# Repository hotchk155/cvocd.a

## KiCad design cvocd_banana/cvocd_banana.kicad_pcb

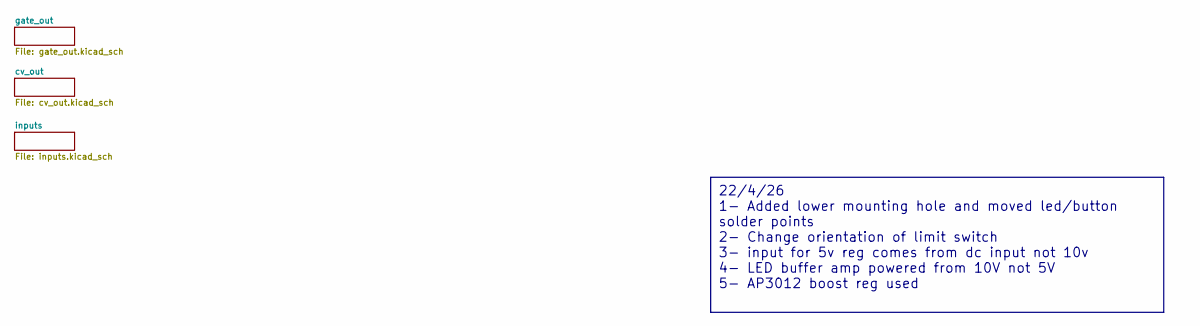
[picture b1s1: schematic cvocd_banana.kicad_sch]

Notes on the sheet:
22/4/26 1- Added lower mounting hole and moved led/button solder points 2- Change orientation of limit switch 3- input for 5v reg comes from dc input not 10v 4- LED buffer amp powered from 10V not 5V 5- AP3012 boost reg used

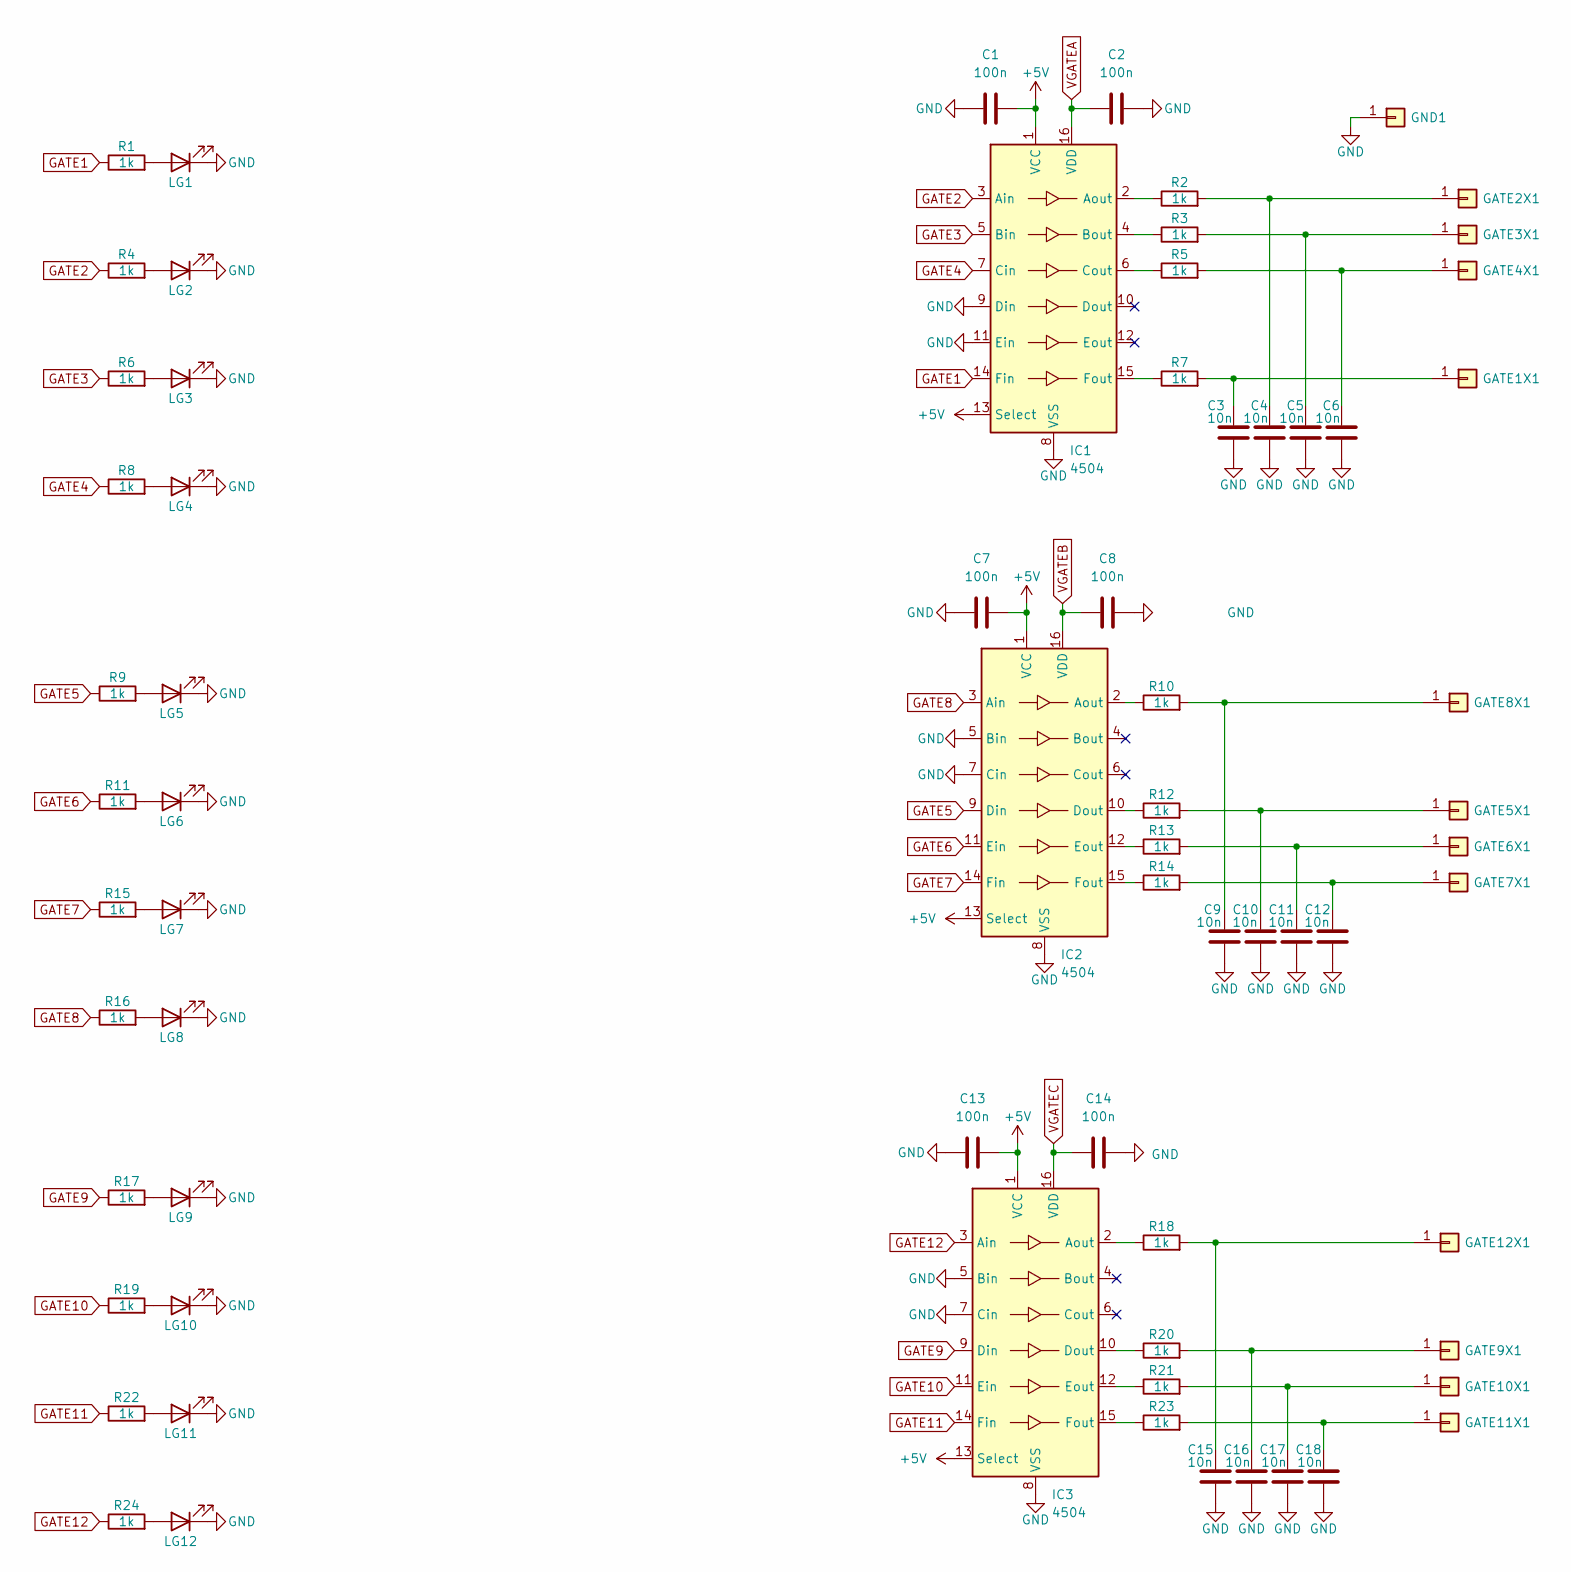
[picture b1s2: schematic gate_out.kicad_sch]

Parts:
C1, C2, C7, C8, C13, C14: 100n; C_0805_2012Metric
C3, C4, C5, C6, C9, C10, C11, C12, C15, C16, C17, C18: 10n; C_0805_2012Metric
GATE1X1, GATE2X1, GATE3X1, GATE4X1, GATE5X1, GATE6X1, GATE7X1, GATE8X1, GATE9X1, GATE10X1, GATE11X1, GATE12X1: Conn_01x01; CINCH-BANANA
GND1: Conn_01x01; CINCH-BANANA
IC1, IC2, IC3: 4504; SOIC-16_3.9x9.9mm_P1.27mm
LG1, LG2, LG3, LG4, LG5, LG6, LG7, LG8, LG9, LG10, LG11, LG12: LED; 3528_ReverseMount_LED
R1, R2, R3, R4, R5, R6, R7, R8, R9, R10, R11, R12, R13, R14, R15, R16, R17, R18, R19, R20, R21, R22, R23, R24: 1k; R_0805_2012Metric

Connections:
+5V: C1.2, C7.2, C13.2, IC1.1 (VCC), IC1.13 (Select), IC2.1 (VCC), IC2.13 (Select), IC3.1 (VCC), IC3.13 (Select); also elsewhere on the board
GATE1: IC1.14 (Fin), R1.1; also elsewhere on the board
GATE2: IC1.3 (Ain), R4.1; also elsewhere on the board
GATE3: IC1.5 (Bin), R6.1; also elsewhere on the board
GATE4: IC1.7 (Cin), R8.1; also elsewhere on the board
GATE5: IC2.9 (Din), R9.1; also elsewhere on the board
GATE6: IC2.11 (Ein), R11.1; also elsewhere on the board
GATE7: IC2.14 (Fin), R15.1; also elsewhere on the board
GATE8: IC2.3 (Ain), R16.1; also elsewhere on the board
GATE9: IC3.9 (Din), R17.1; also elsewhere on the board
GATE10: IC3.11 (Ein), R19.1; also elsewhere on the board
GATE11: IC3.14 (Fin), R22.1; also elsewhere on the board
GATE12: IC3.3 (Ain), R24.1; also elsewhere on the board
GND: C1.1, C2.2, C3.1, C4.1, C5.1, C6.1, C7.1, C8.2, C9.1, C10.1, C11.1, C12.1, C13.1, C14.2, C15.1, C16.1, C17.1, C18.1, GND1.1, IC1.8 (VSS), IC1.9 (Din), IC1.11 (Ein), IC2.5 (Bin), IC2.7 (Cin), IC2.8 (VSS), IC3.5 (Bin), IC3.7 (Cin), IC3.8 (VSS), LG1.1 (K), LG2.1 (K), LG3.1 (K), LG4.1 (K), LG5.1 (K), LG6.1 (K), LG7.1 (K), LG8.1 (K), LG9.1 (K), LG10.1 (K), LG11.1 (K), LG12.1 (K); also elsewhere on the board
unnamed: C3.2, GATE1X1.1, R7.2
unnamed: C4.2, GATE2X1.1, R2.2
unnamed: C5.2, GATE3X1.1, R3.2
unnamed: C6.2, GATE4X1.1, R5.2
unnamed: C10.2, GATE5X1.1, R12.2
unnamed: C11.2, GATE6X1.1, R13.2
unnamed: C12.2, GATE7X1.1, R14.2
unnamed: C9.2, GATE8X1.1, R10.2
unnamed: C16.2, GATE9X1.1, R20.2
unnamed: C17.2, GATE10X1.1, R21.2
unnamed: C18.2, GATE11X1.1, R23.2
unnamed: C15.2, GATE12X1.1, R18.2
unnamed: IC1.2 (Aout), R2.1
unnamed: IC1.4 (Bout), R3.1
unnamed: IC1.6 (Cout), R5.1
unnamed: IC1.15 (Fout), R7.1
unnamed: IC2.2 (Aout), R10.1
unnamed: IC2.10 (Dout), R12.1
unnamed: IC2.12 (Eout), R13.1
unnamed: IC2.15 (Fout), R14.1
unnamed: IC3.2 (Aout), R18.1
unnamed: IC3.10 (Dout), R20.1
unnamed: IC3.12 (Eout), R21.1
unnamed: IC3.15 (Fout), R23.1
unnamed: LG1.2 (A), R1.2
unnamed: LG2.2 (A), R4.2
unnamed: LG3.2 (A), R6.2
unnamed: LG4.2 (A), R8.2
unnamed: LG5.2 (A), R9.2
unnamed: LG6.2 (A), R11.2
unnamed: LG7.2 (A), R15.2
unnamed: LG8.2 (A), R16.2
unnamed: LG9.2 (A), R17.2
unnamed: LG10.2 (A), R19.2
unnamed: LG11.2 (A), R22.2
unnamed: LG12.2 (A), R24.2
VGATEA: C2.1, IC1.16 (VDD); also elsewhere on the board
VGATEB: C8.1, IC2.16 (VDD); also elsewhere on the board
VGATEC: C14.1, IC3.16 (VDD); also elsewhere on the board

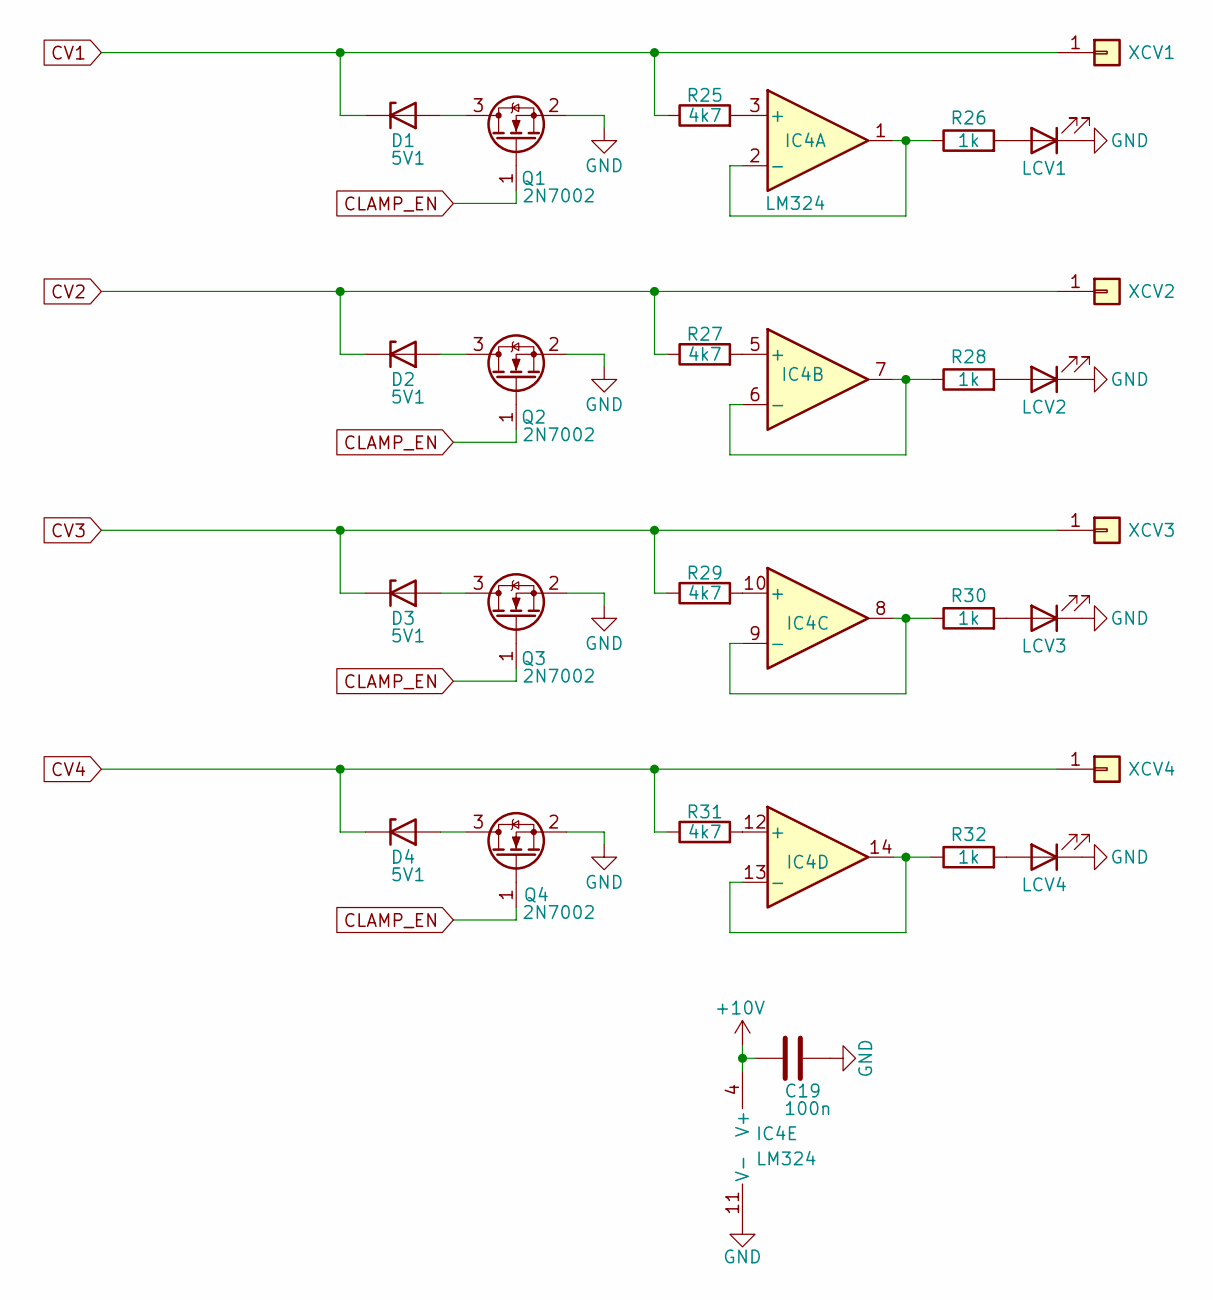
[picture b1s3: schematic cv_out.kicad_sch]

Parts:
C19: 100n; C_0805_2012Metric
D1, D2, D3, D4: 5V1; D_0805_2012Metric
IC4: LM324; SO-14_3.9x8.65mm_P1.27mm
LCV1, LCV2, LCV3, LCV4: LED; 3528_ReverseMount_LED
Q1, Q2, Q3, Q4: 2N7002; SOT-23
R25, R27, R29, R31: 4k7; R_0805_2012Metric
R26, R28, R30, R32: 1k; R_0805_2012Metric
XCV1, XCV2, XCV3, XCV4: Conn_01x01; CINCH-BANANA

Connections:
+10V: C19.1, IC4.4 (V+); also elsewhere on the board
CLAMP_EN: Q1.1 (G), Q2.1 (G), Q3.1 (G), Q4.1 (G); also elsewhere on the board
CV1: D1.1 (K), R25.1, XCV1.1; also elsewhere on the board
CV2: D2.1 (K), R27.1, XCV2.1; also elsewhere on the board
CV3: D3.1 (K), R29.1, XCV3.1; also elsewhere on the board
CV4: D4.1 (K), R31.1, XCV4.1; also elsewhere on the board
GND: C19.2, IC4.11 (V-), LCV1.1 (K), LCV2.1 (K), LCV3.1 (K), LCV4.1 (K), Q1.2 (S), Q2.2 (S), Q3.2 (S), Q4.2 (S); also elsewhere on the board
unnamed: D1.2 (A), Q1.3 (D)
unnamed: D2.2 (A), Q2.3 (D)
unnamed: D3.2 (A), Q3.3 (D)
unnamed: D4.2 (A), Q4.3 (D)
unnamed: IC4.3 (+), R25.2
unnamed: IC4.1, IC4.2 (-), R26.1
unnamed: IC4.5 (+), R27.2
unnamed: IC4.6 (-), IC4.7, R28.1
unnamed: IC4.10 (+), R29.2
unnamed: IC4.8, IC4.9 (-), R30.1
unnamed: IC4.12 (+), R31.2
unnamed: IC4.13 (-), IC4.14, R32.1
unnamed: LCV1.2 (A), R26.2
unnamed: LCV2.2 (A), R28.2
unnamed: LCV3.2 (A), R30.2
unnamed: LCV4.2 (A), R32.2

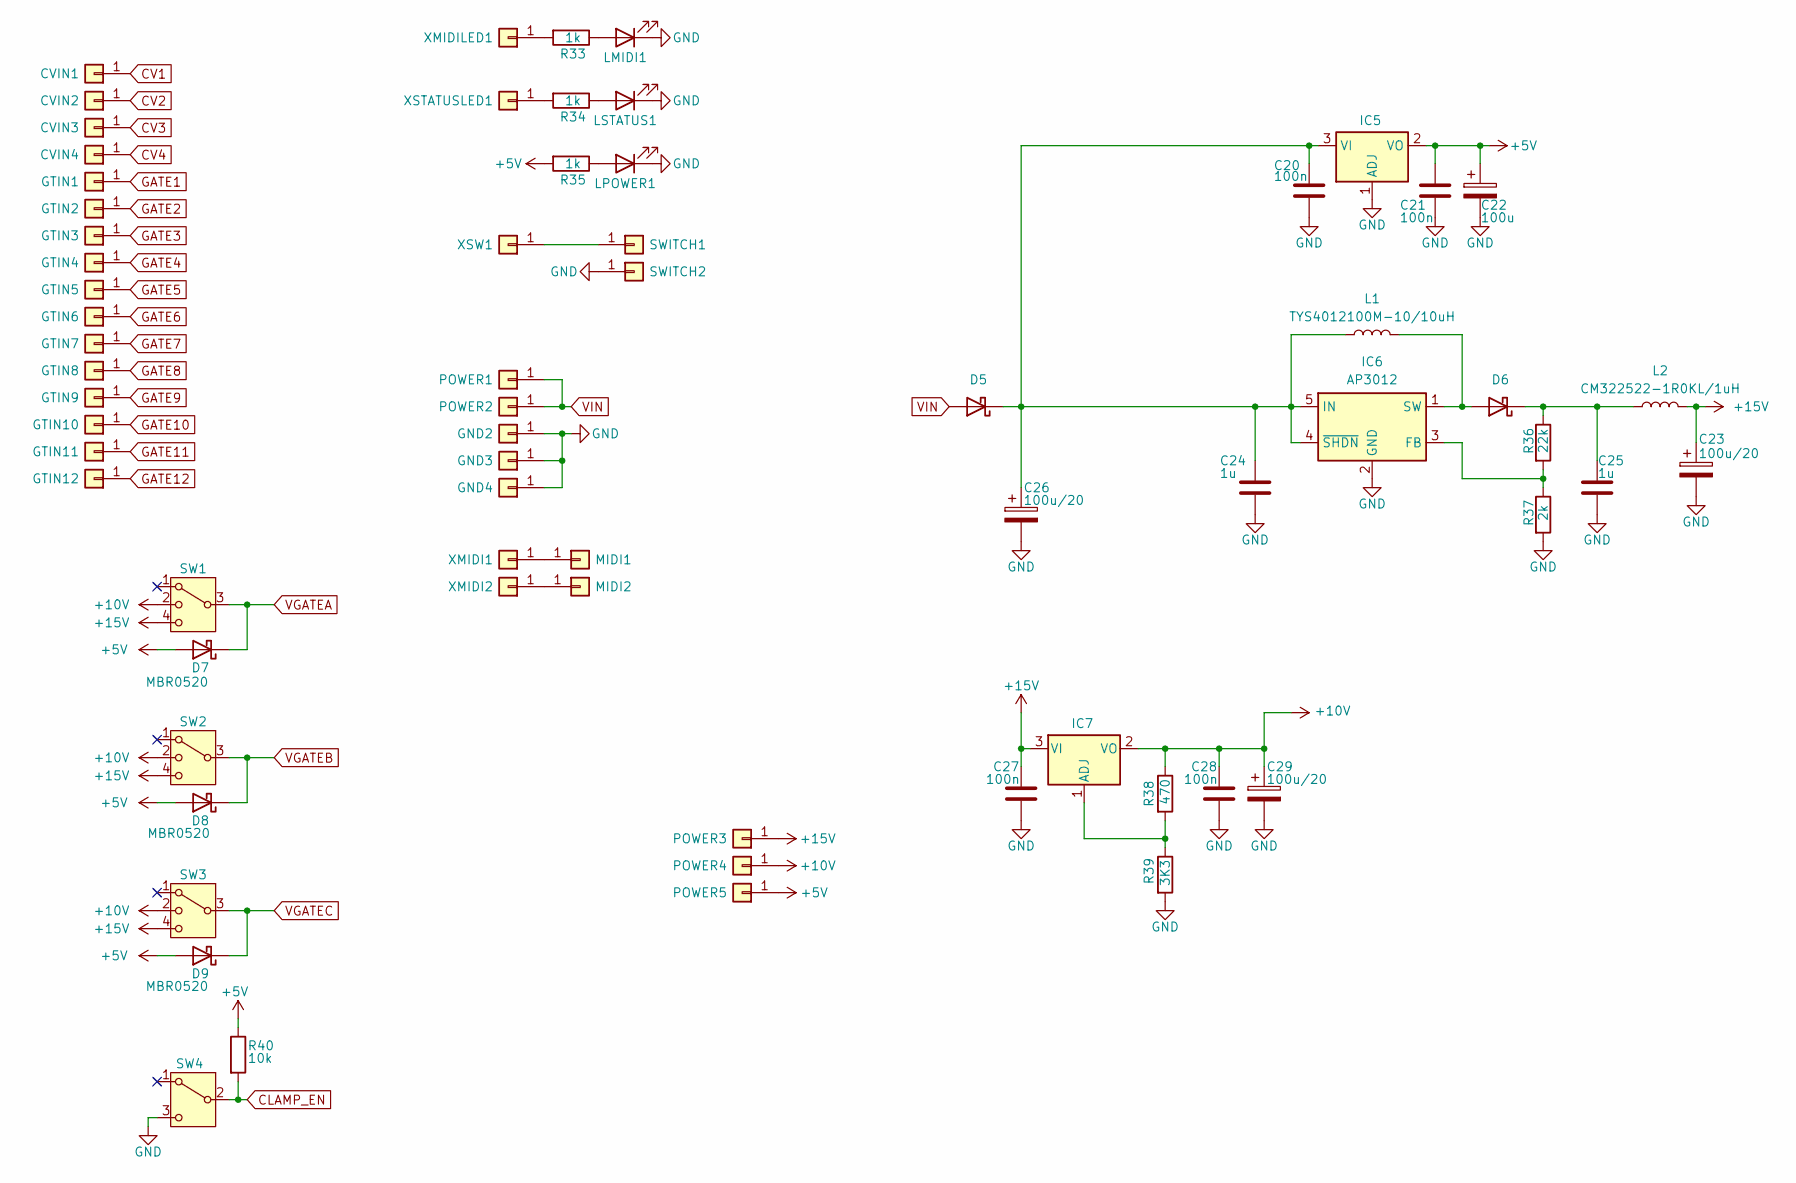
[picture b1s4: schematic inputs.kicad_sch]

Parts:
C20, C21, C27, C28: 100n; C_0805_2012Metric
C22: 100u; CP_EIA-7343-31_Kemet-D
C23, C26, C29: 100u/20; CP_EIA-7343-31_Kemet-D
C24, C25: 1u; C_0805_2012Metric
CVIN1, CVIN2, CVIN3, CVIN4: Conn_01x01; WireToBoardCVOCD
D5, D6: D_Schottky; D_SOD-123
D7, D8, D9: MBR0520; D_SOD-123
GND2, GND3, GND4: Conn_01x01; WireToBoardCVOCD
GTIN1, GTIN2, GTIN3, GTIN4, GTIN5, GTIN6, GTIN7, GTIN8, GTIN9, GTIN10, GTIN11, GTIN12: Conn_01x01; WireToBoardCVOCD
IC5: AMS1117; SOT-223-3_TabPin2
IC6: AP3012; SOT-23-5
IC7: LM317L_SOT-89; SOT-223-3_TabPin2
L1: TYS4012100M-10/10uH; L_Taiyo-Yuden_MD-4040
L2: CM322522-1R0KL/1uH; L_1210_3225Metric
LMIDI1: LED; 3528_ReverseMount_LED
LPOWER1: LED; 3528_ReverseMount_LED
LSTATUS1: LED; 3528_ReverseMount_LED
MIDI1, MIDI2: Conn_01x01; WireToBoardCVOCD
POWER1, POWER2, POWER3, POWER4, POWER5: Conn_01x01; WireToBoardCVOCD
R33, R34, R35: 1k; R_0805_2012Metric
R36: 22k; R_0805_2012Metric
R37: 2k; R_0805_2012Metric
R38: 470; R_0805_2012Metric
R39: 3K3; R_0805_2012Metric
R40: 10k; R_0805_2012Metric
SW1, SW2, SW3: SW_SP3T; Slide_1P3T_Rev_Mnt_CLSB13B01
SW4: SW_SPDT; Slide_1P2T_Rev_Mnt_CLSB12B01
SWITCH1, SWITCH2: Conn_01x01; WireToBoardCVOCD
XMIDI1, XMIDI2: Conn_01x01; WireToBoardCVOCD
XMIDILED1: Conn_01x01; WireToBoardCVOCD
XSTATUSLED1: Conn_01x01; WireToBoardCVOCD
XSW1: Conn_01x01; WireToBoardCVOCD

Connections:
+5V: C21.1, C22.1, D7.2 (A), D8.2 (A), D9.2 (A), IC5.2 (VO), POWER5.1, R35.2, R40.1; also elsewhere on the board
+10V: C28.1, C29.1, IC7.2 (VO), POWER4.1, R38.1, SW1.2, SW2.2, SW3.2; also elsewhere on the board
+15V: C23.1, C27.1, IC7.3 (VI), L2.2, POWER3.1, SW1.4, SW2.4, SW3.4
CLAMP_EN: R40.2, SW4.2 (B); also elsewhere on the board
CV1: CVIN1.1; also elsewhere on the board
CV2: CVIN2.1; also elsewhere on the board
CV3: CVIN3.1; also elsewhere on the board
CV4: CVIN4.1; also elsewhere on the board
GATE1: GTIN1.1; also elsewhere on the board
GATE2: GTIN2.1; also elsewhere on the board
GATE3: GTIN3.1; also elsewhere on the board
GATE4: GTIN4.1; also elsewhere on the board
GATE5: GTIN5.1; also elsewhere on the board
GATE6: GTIN6.1; also elsewhere on the board
GATE7: GTIN7.1; also elsewhere on the board
GATE8: GTIN8.1; also elsewhere on the board
GATE9: GTIN9.1; also elsewhere on the board
GATE10: GTIN10.1; also elsewhere on the board
GATE11: GTIN11.1; also elsewhere on the board
GATE12: GTIN12.1; also elsewhere on the board
GND: C20.2, C21.2, C22.2, C23.2, C24.2, C25.2, C26.2, C27.2, C28.2, C29.2, GND2.1, GND3.1, GND4.1, IC5.1 (ADJ), IC6.2 (GND), LMIDI1.1 (K), LPOWER1.1 (K), LSTATUS1.1 (K), R37.2, R39.2, SW4.3 (C), SWITCH2.1; also elsewhere on the board
unnamed: C20.1, C24.1, C26.1, D5.1 (K), IC5.3 (VI), IC6.4 (~SHDN), IC6.5 (IN), L1.1
unnamed: D6.2 (A), IC6.1 (SW), L1.2
unnamed: C25.1, D6.1 (K), L2.1, R36.1
unnamed: IC6.3 (FB), R36.2, R37.1
unnamed: IC7.1 (ADJ), R38.2, R39.1
unnamed: LMIDI1.2 (A), R33.1
unnamed: LPOWER1.2 (A), R35.1
unnamed: LSTATUS1.2 (A), R34.1
unnamed: MIDI1.1, XMIDI1.1
unnamed: MIDI2.1, XMIDI2.1
unnamed: SWITCH1.1, XSW1.1
unnamed: R33.2, XMIDILED1.1
unnamed: R34.2, XSTATUSLED1.1
VGATEA: D7.1 (K), SW1.3; also elsewhere on the board
VGATEB: D8.1 (K), SW2.3; also elsewhere on the board
VGATEC: D9.1 (K), SW3.3; also elsewhere on the board
VIN: D5.2 (A), POWER1.1, POWER2.1

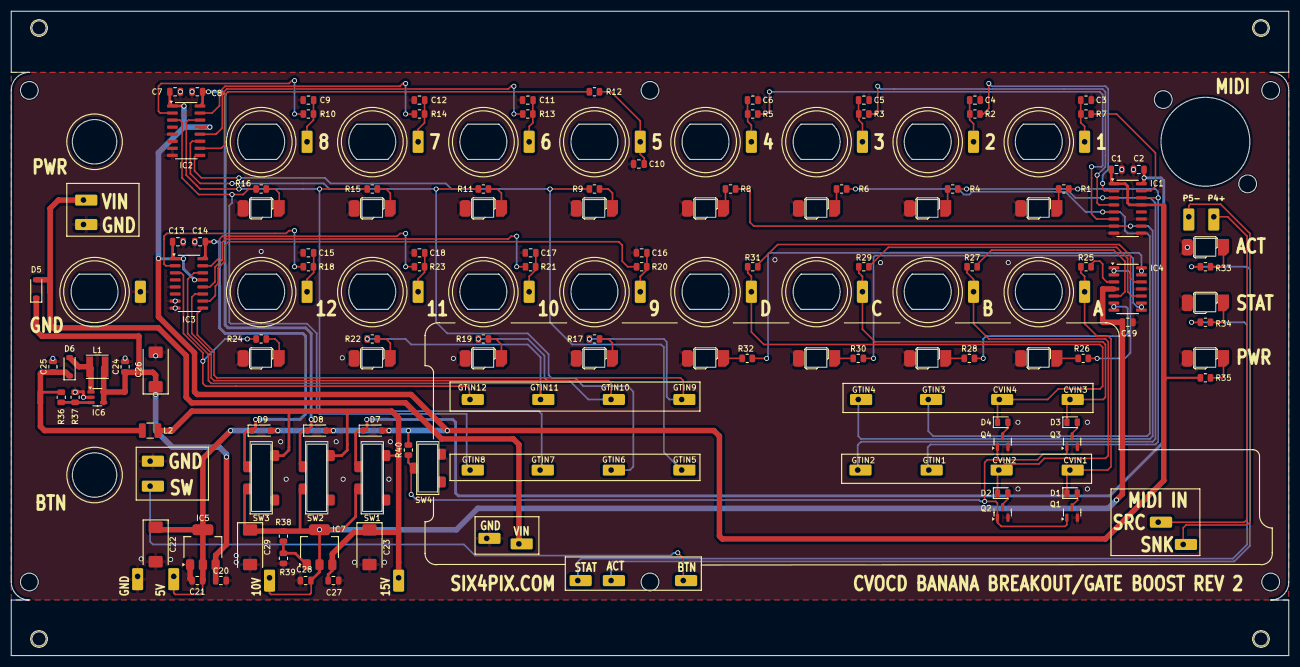
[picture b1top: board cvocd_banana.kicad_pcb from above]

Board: 2 copper layers, 230.0 x 115.9 mm, 164 parts (0 on the bottom side), 90 nets.

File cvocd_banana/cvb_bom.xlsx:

Designator | Footprint |  | Quantity | Designation | 50
C1, C2, C7, C8, C13, C14, C19, C20, C21, C27, C28 | C0805 | 100n | 12 | 100n | 600
C22, C23, C26, C29 | D CASE | 100uF | 4 | TAJD107K020SNTV | 200 | 0.43
C24, C25 | C0805 | 1uF | 2 | CL21B105KAFNNNG | 100 | 0.02
C3, C4, C5, C6, C9, C10, C11, C12, C15, C16, C17, C18 | C0805 | 10n | 12 | 10n | 600
CVA, CVB, CVC, CVD | 108-0910-001 |  | 4 | Banana Blue | 200 | 0.68
D1, D2, D3, D4 | D0805 |  | 4 | BZY55B5V1 RBG | 200 | 0.1
D5, D6, D7, D8, D9 | SOD123 |  | 5 | MBR0520LT | 250 | 0.09
GND | 108-0903-001 |  | 1 | Banana Black | 50 | 0.68
GT1, GT2, GT3, GT4, GT5, GT6, GT7, GT8, GT9, GT10, GT11, GT12 | 108-0902-001 |  | 12 | Banana Red | 600 | 0.65
IC3, IC1, IC2 | SOIC16 |  | 3 | MC14504BDR2G | 150 | 0.3
IC4 | SOIC14 |  | 1 | LM324BIDR | 50 | 0.12
IC5 | SOT223 |  | 1 | TLV76150DCYR | 50 | 0.23
IC6 | SOT-23-5 |  | 1 | AP3012KTR-E1 | 50 | 0.25
IC7 | SOT223 |  | 1 | LM317MBSTT3G | 50 | 0.2
L1 |  |  | 1 | TYS4012100M-10 | 50 | 0.28999999999999998
L2 |  |  | 1 | CM322522-1R0KL | 50 | 0.15
LCV1, LCV2, LCV3, LCV4, LG1, LG2, LG3, LG4, LG5, LG6, LG7, LG8, LG9, LG10, LG11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 | 3258 Reverse Mount |  | 17 | LED RED | 850
LMIDI1 | 3258 Reverse Mount |  | 1 | LED BLUE | 50
LSTATUS1 | 3258 Reverse Mount |  | 1 | LED YELLOW | 50
MIDI SOCKET |  |  | 1 | SWITCH ELEC | 50
POWER SOCKET |  |  | 1 |  | 50
PUSH BUTTON |  |  | 1 |  | 50
Q2,Q1,Q4,Q3 | SOT-23 |  | 4 | 2N7002 | 200 | 0.16
R1, R2, R3, R4 R5, R6, R7, R8, R9, R10, R11, R12, R13, R14, R15, R16, R17, R18,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 | R0805 |  | 31 | 1k | 1550
R25,R27,R29,R31 | R0805 |  | 4 | 4k7 | 200
R36 | R_0805_2012Metric |  | 1 | 22k | 50
R37 | R0805 |  | 1 | 2k | 50
R38 | R0805 |  | 1 | 470R | 50
R39 | R0805 |  | 1 | 3K3 | 50
R40 | R0805 |  | 1 | 10k | 50
SW1, SW2, SW3 | CL-SB-13B-02T |  | 3 | SW_SP3T | 150 | 0.95
SW4 | CL-SB-12B-01T |  | 1 | SW_SPDT | 50 | 0.65

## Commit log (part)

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2016-02-05 :circus_tent: Added .gitattributes & .gitignore files
2016-02-11 getting there
2016-02-11 almost done?
2016-02-11 tweaks
2016-03-05 pcb v1
2016-03-23 initial version
2016-03-23 add comp values
2016-03-25 firmware
2016-03-26 working on it
2016-04-03 in progress
2016-04-09 stuff
2016-05-07 test release 0.1
2016-05-09 rev0.2
2016-05-23 fixes
    fix pitch bend, reset cv to zero
2016-05-23 retrigs, pitch bend cv, fixes
2016-05-24 auto save, bpm to cv, cc to cv
2016-05-24 test voltage, clock
2016-05-24 rev0.3
2016-05-26 bit of tidying up
2016-05-29 rev2 updates - checking needed
2016-06-10 extra n fet on voltage select circuits
2016-06-13 PCBrev2
2016-06-13 Final rev 2 release PCB
2016-06-14 REV2A
    fixed some DRC issues
2016-07-08 updates for new shift reg
2016-07-08 16bit dac changes
2016-07-09 cv mods
2016-07-16 working on rev 3 LPC812
2016-07-18 mods
2016-07-18 rev3 PCB final
2016-07-23 label changes only
2016-08-12 Reverting master back to original PIC code for 12bit DAC
2016-08-24 working on CV gate mode
2016-08-24 rename
2016-09-26 Revert "working on CV gate mode"
    This reverts commit b332149b2ce033c2ec8ef14785a9b57907feba7d.
2016-09-26 test program updated
2016-09-26 1.0 release candidate
2016-10-14 various mods and fixes
2016-10-14 remove split message for now
2016-10-14 fixes from tests
2016-10-14 Slot stealing in chord mode
2016-10-17 user guide
2016-10-17 docs
2016-10-17 note range
2016-10-24 packing slip
2016-10-24 Revert "packing slip"
    This reverts commit 48e4d3a89401627845a863b18054c9caac200d1a.
2016-11-10 reorg
2016-11-11 Hz/Volt
2016-11-11 1.1beta
2017-01-30 transport toggle mode
2017-02-12 1.3beta
    fix to CC channel handling
2017-04-03 rev2
2017-05-20 rev2.1 Fix issue with negative transpose amounts
2017-05-20 rev2.2 1.2V/oct
2017-10-01 2.2BETA -> REV3
2017-10-01 rename 3->3.0
2017-10-14 rebuild after config page fix
2017-10-14 rebuild with new web page
2017-12-09 smts moved to top of board
2017-12-10 pcb bitmap
2017-12-10 license logo
2017-12-10 tidy up silk
2017-12-30 icsp to top layer, current lim resistors
2018-01-02 adding teensy test rig sketch
2018-01-03 3.1 beta - add calibration features / temp remove BPM->CV
2018-01-03 keep __f file!
2018-01-03 3.1beta
2018-01-03 hshs
2018-01-22 V3 possible final..
2018-01-23 Revert "aaa"
    This reverts commit 3954c3311754772a76ec03b990afd23774723b60.
2018-01-28 working on v4
2018-01-30 REV4 RELEASE CANDIDATE
2018-02-19 v5 board first version
2018-02-22 v5 pcb release candidate
2018-03-12 V5.1 SILK SCREEN UPDATES
2018-05-12 rev4.0
2018-05-24 Fix issue with skipping system common messages with parameters
2018-06-11 mtc fix
2018-07-04 triangle waves
2018-07-13 following fix to web page
2018-07-19 before new board
2018-07-21 backup
2018-07-21 more updates
2018-07-22 work
2018-07-22 old version
2018-07-22 final tweaks
2018-09-10 rev 4.1 beta
    correct an issue where midi note gates could trigger on any note when on same midi channel as a note input
2018-09-10 add 4.1 and 4.2 to archive folder
2018-09-10 no change
2018-12-15 midi spec added
2018-12-22 config page
2018-12-23 ssss
2018-12-27 dsfs
2018-12-27 cvocfg
2019-01-06 gfdg
2019-01-24 4.2beta->5 release
2019-01-24 label
2019-02-25 5.1BETA
    Improvement to monophonic note modes to allow paraphonic operation. Fix stuck note gate issue due to deferred gate on events
2019-04-23 add config spec
2019-06-18 paraphonic chord note added
2019-06-18 5.2 beta
2020-01-17 V6 candidate
    change polarity on mini midi in socket
2020-03-26 REV 6A - Diode direction marking only
2020-04-28 gate 12 description
2020-06-28 PCB front panel
2020-06-28 move config page
2020-07-07 Bump electron from 4.0.0 to 7.2.4 in /cvocfg
    Bumps [electron](https://github.com/electron/electron) from 4.0.0 to 7.2.4.
    - [Release notes](https://github.com/electron/electron/releases)
    - [Changelog](https://github.com/electron/electron/blob/master/docs/breaking-changes.md)
    - [Commits](https://github.com/electron/electron/compare/v4.0.0...v7.2.4)
2021-01-26 TRS MMA
2021-01-28 Bump electron from 4.0.0 to 9.4.0 in /cvocfg
    Bumps [electron](https://github.com/electron/electron) from 4.0.0 to 9.4.0.
    - [Release notes](https://github.com/electron/electron/releases)
    - [Changelog](https://github.com/electron/electron/blob/master/docs/breaking-changes.md)
    - [Commits](https://github.com/electron/electron/compare/v4.0.0...v9.4.0)
2021-10-12 Bump electron from 4.0.0 to 11.5.0 in /cvocfg
    Bumps [electron](https://github.com/electron/electron) from 4.0.0 to 11.5.0.
    - [Release notes](https://github.com/electron/electron/releases)
    - [Changelog](https://github.com/electron/electron/blob/main/docs/breaking-changes.md)
    - [Commits](https://github.com/electron/electron/compare/v4.0.0...v11.5.0)
    ---
    updated-dependencies:
2022-03-25 Bump electron from 4.0.0 to 13.6.6 in /cvocfg
    Bumps [electron](https://github.com/electron/electron) from 4.0.0 to 13.6.6.
    - [Release notes](https://github.com/electron/electron/releases)
    - [Changelog](https://github.com/electron/electron/blob/main/docs/breaking-changes.md)
    - [Commits](https://github.com/electron/electron/compare/v4.0.0...v13.6.6)
    ---
    updated-dependencies:
2022-06-13 test rig change
2022-06-16 Bump electron from 4.0.0 to 15.5.5 in /cvocfg
    Bumps [electron](https://github.com/electron/electron) from 4.0.0 to 15.5.5.
    - [Release notes](https://github.com/electron/electron/releases)
    - [Changelog](https://github.com/electron/electron/blob/main/docs/breaking-changes.md)
    - [Commits](https://github.com/electron/electron/compare/v4.0.0...v15.5.5)
    ---
    updated-dependencies:
2022-07-27 A6 test firmware
2022-07-27 add source images
2022-08-29 add async sending to cal tool
2022-11-02 add A0 to archive
2022-11-10 Bump electron from 4.0.0 to 18.3.7 in /cvocfg
    Bumps [electron](https://github.com/electron/electron) from 4.0.0 to 18.3.7.
    - [Release notes](https://github.com/electron/electron/releases)
    - [Changelog](https://github.com/electron/electron/blob/main/docs/breaking-changes.md)
    - [Commits](https://github.com/electron/electron/compare/v4.0.0...v18.3.7)
    ---
    updated-dependencies:
2022-11-27 initial experimental build with MPLAB.X
2023-02-28 Bump minimist and extract-zip in /cvocfg
    Bumps [minimist](https://github.com/minimistjs/minimist) and [extract-zip](https://github.com/maxogden/extract-zip). These dependencies needed to be updated together.
    Updates `minimist` from 1.2.0 to 1.2.8
    - [Release notes](https://github.com/minimistjs/minimist/releases)
    - [Changelog](https://github.com/minimistjs/minimist/blob/main/CHANGELOG.md)
    - [Commits](https://github.com/minimistjs/minimist/compare/v1.2.0...v1.2.8)
    Updates `extract-zip` from 1.6.7 to 1.7.0
2023-04-17 Bump json-schema and jsprim in /cvocfg
    Bumps [json-schema](https://github.com/kriszyp/json-schema) and [jsprim](https://github.com/joyent/node-jsprim). These dependencies needed to be updated together.
    Updates `json-schema` from 0.2.3 to 0.4.0
    - [Release notes](https://github.com/kriszyp/json-schema/releases)
    - [Commits](https://github.com/kriszyp/json-schema/compare/v0.2.3...v0.4.0)
    Updates `jsprim` from 1.4.1 to 1.4.2
    - [Release notes](https://github.com/joyent/node-jsprim/releases)
2023-04-17 Bump ajv from 6.6.2 to 6.12.6 in /cvocfg
    Bumps [ajv](https://github.com/ajv-validator/ajv) from 6.6.2 to 6.12.6.
    - [Release notes](https://github.com/ajv-validator/ajv/releases)
    - [Commits](https://github.com/ajv-validator/ajv/compare/v6.6.2...v6.12.6)
    ---
    updated-dependencies:
    - dependency-name: ajv
2025-04-09 test firmware update
2026-02-02 add manual images
2026-02-02 chord mode changes in progress
2026-02-03 changes to chord modes
2026-02-03 chord mode updates
2026-02-04 chord mode changes complete and tested
2026-02-06 chord mode changes following hardware tests
2026-02-06 add 5.2 and 5.3 SYSEX files to release folders
2026-02-06 update to midi spec
2026-02-06 updates to UI for rev 5.3
2026-02-11 manual update 5.3
2026-02-11 initial XC8 for vscode build
2026-02-11 xc8 updates
2026-02-13 slew/glide/bpmtocv
2026-02-26 remove old MPLABX project
2026-03-26 banana board in progress
2026-03-26 REV1
2026-03-27 updates to banana pcb
2026-03-27 fascia
2026-03-28 pcb and fascia version 1
2026-04-17 additional mounting holes on fascia
2026-04-21 banana updates
2026-04-22 banana pcb main v2
2026-04-23 PCB V2
2026-06-17 5.0X reset gates at startup
2026-06-17 add 5.0x to releases
2026-06-17 v3 test firmware for faster scan
2026-06-18 packing slip-
